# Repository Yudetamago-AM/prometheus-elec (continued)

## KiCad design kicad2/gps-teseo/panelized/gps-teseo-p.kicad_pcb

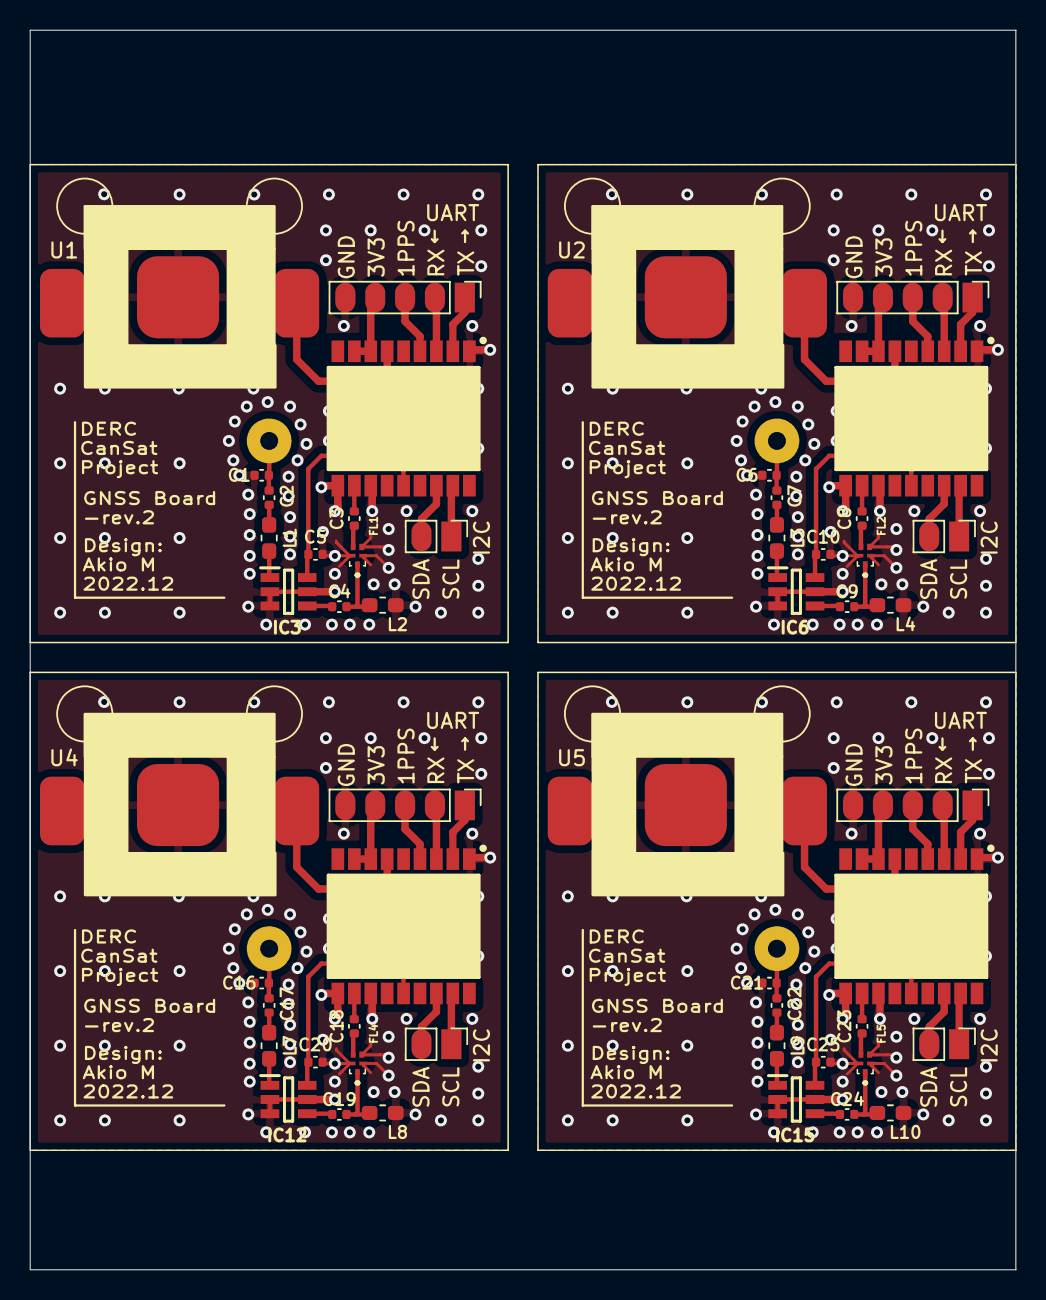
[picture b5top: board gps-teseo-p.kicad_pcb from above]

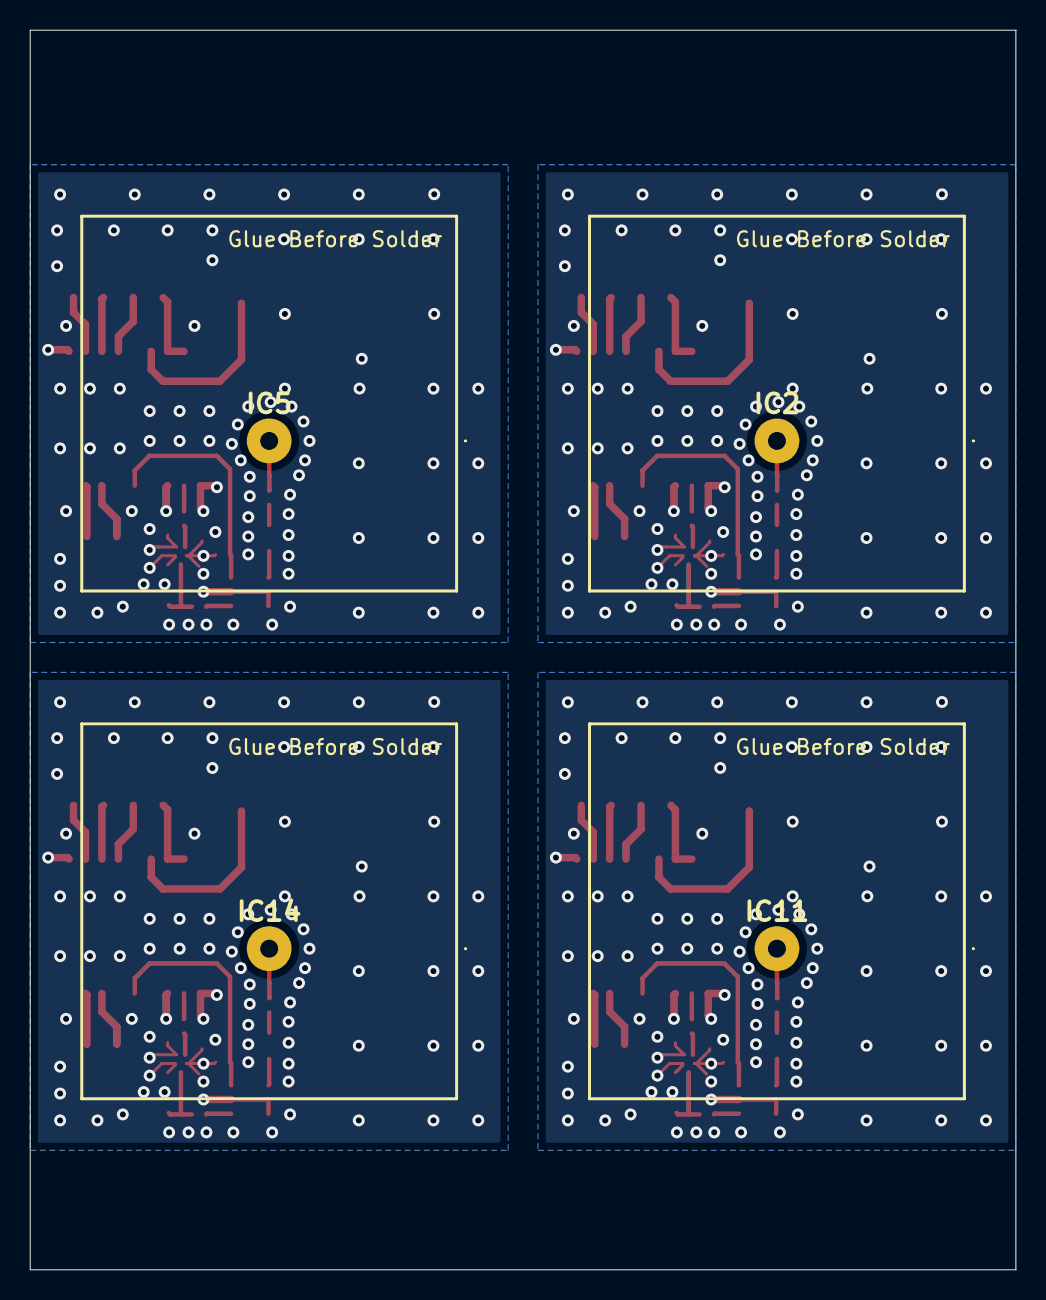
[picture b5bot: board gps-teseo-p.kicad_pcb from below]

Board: 4 copper layers, 66.0 x 83.0 mm, 56 parts (4 on the bottom side), 16 nets.

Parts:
C1, C6, C16, C21: 1p; C_0402_1005Metric
C2, C4, C7, C9, C17, C19, C22, C24: 100p; C_0402_1005Metric
C3, C8, C18, C23: 120p; C_0402_1005Metric
C5, C10, C20, C25: 470p; C_0402_1005Metric
FL1, FL2, FL4, FL5: SAFEA1G58KA0F00R15
IC1, IC4, IC10, IC13: TESEO-LIV3F; SON110P970X1010X230-18N
IC2, IC5, IC11, IC14: CGGBPD.25.A; CGGBPD25A
IC3, IC6, IC12, IC15: MAX2641EUT+T; SOT95P280X145-6N
J1, J3, J7, J9: Conn_01x05_Male; PinHeader_1x05_P2.00mm_Vertical
J2, J4, J8, J10: I2C; PinHeader_1x02_P2.00mm_Vertical
L1, L3, L7, L9: 5.6n; L_0603_1608Metric_Pad1.05x0.95mm_HandSolder
L2, L4, L8, L10: 6.8n; L_0603_1608Metric_Pad1.05x0.95mm_HandSolder
U1, U2, U4, U5: CR1025; CR1025_Holder

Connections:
+3V0: IC1.6 (VBATT), IC4.6 (VBATT), IC10.6 (VBATT), IC13.6 (VBATT), U1.2 (plus), U2.2 (plus), U4.2 (plus), U5.2 (plus)
+3V3: IC1.7 (VCC_IO), IC1.8 (VCC), IC4.7 (VCC_IO), IC4.8 (VCC), IC10.7 (VCC_IO), IC10.8 (VCC), IC13.7 (VCC_IO), IC13.8 (VCC), J1.4, J3.4, J7.4, J9.4
/GNSS_1PPS: IC1.4 (1PPS), IC4.4 (1PPS), IC10.4 (1PPS), IC13.4 (1PPS), J1.3, J3.3, J7.3, J9.3
/GNSS_RX: IC1.3 (RX), IC4.3 (RX), IC10.3 (RX), IC13.3 (RX), J1.2, J3.2, J7.2, J9.2
/GNSS_TX: IC1.2 (TX), IC4.2 (TX), IC10.2 (TX), IC13.2 (TX), J1.1, J3.1, J7.1, J9.1
/SCL: IC1.17 (SCL), IC4.17 (SCL), IC10.17 (SCL), IC13.17 (SCL), J2.1, J4.1, J8.1, J10.1
/SDA: IC1.16 (SDA), IC4.16 (SDA), IC10.16 (SDA), IC13.16 (SDA), J2.2, J4.2, J8.2, J10.2
/VCC_RF: C5.1, C10.1, C20.1, C25.1, IC1.14 (VCC_RF), IC3.6 (VCC), IC4.14 (VCC_RF), IC6.6 (VCC), IC10.14 (VCC_RF), IC12.6 (VCC), IC13.14 (VCC_RF), IC15.6 (VCC)
GND2: C1.2, C5.2, C6.2, C10.2, C16.2, C20.2, C21.2, C25.2, FL1.2 (GND_1), FL1.3 (GND_2), FL1.5 (GND_3), FL2.2 (GND_1), FL2.3 (GND_2), FL2.5 (GND_3), FL4.2 (GND_1), FL4.3 (GND_2), FL4.5 (GND_3), FL5.2 (GND_1), FL5.3 (GND_2), FL5.5 (GND_3), IC1.1 (GND), IC1.10 (GND_RF_1), IC1.12 (GND_RF_2), IC3.2 (GND_1), IC3.3 (GND_2), IC3.5 (GND_3), IC4.1 (GND), IC4.10 (GND_RF_1), IC4.12 (GND_RF_2), IC6.2 (GND_1), IC6.3 (GND_2), IC6.5 (GND_3), IC10.1 (GND), IC10.10 (GND_RF_1), IC10.12 (GND_RF_2), IC12.2 (GND_1), IC12.3 (GND_2), IC12.5 (GND_3), IC13.1 (GND), IC13.10 (GND_RF_1), IC13.12 (GND_RF_2), IC15.2 (GND_1), IC15.3 (GND_2), IC15.5 (GND_3), J1.5, J3.5, J7.5, J9.5, L2.2, L4.2, L8.2, L10.2, U1.1 (minus), U2.1 (minus), U4.1 (minus), U5.1 (minus)
unnamed: C1.1, C2.1, C6.1, C7.1, C16.1, C17.1, C21.1, C22.1, IC2.1, IC5.1, IC11.1, IC14.1
unnamed: C2.2, C7.2, C17.2, C22.2, L1.1, L3.1, L7.1, L9.1
unnamed: C3.1, C8.1, C18.1, C23.1, FL1.4 (OUT), FL2.4 (OUT), FL4.4 (OUT), FL5.4 (OUT)
unnamed: C3.2, C8.2, C18.2, C23.2, IC1.11 (RF_IN), IC4.11 (RF_IN), IC10.11 (RF_IN), IC13.11 (RF_IN)
unnamed: C4.1, C9.1, C19.1, C24.1, IC3.4 (RFOUT), IC6.4 (RFOUT), IC12.4 (RFOUT), IC15.4 (RFOUT)
unnamed: C4.2, C9.2, C19.2, C24.2, FL1.1 (IN), FL2.1 (IN), FL4.1 (IN), FL5.1 (IN), L2.1, L4.1, L8.1, L10.1
unnamed: IC3.1 (RFIN), IC6.1 (RFIN), IC12.1 (RFIN), IC15.1 (RFIN), L1.2, L3.2, L7.2, L9.2

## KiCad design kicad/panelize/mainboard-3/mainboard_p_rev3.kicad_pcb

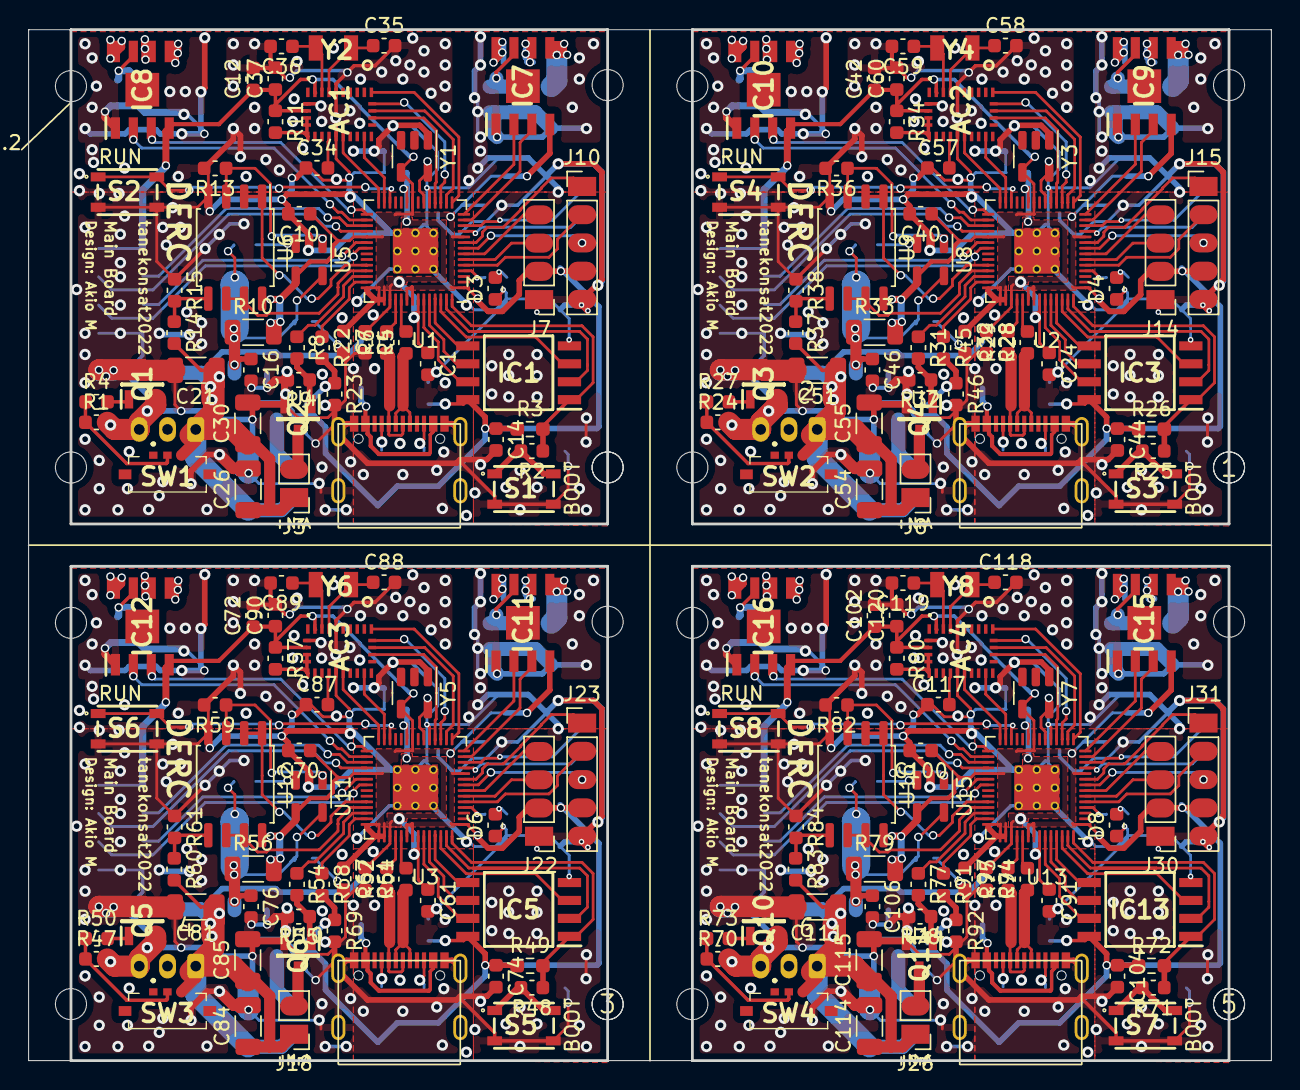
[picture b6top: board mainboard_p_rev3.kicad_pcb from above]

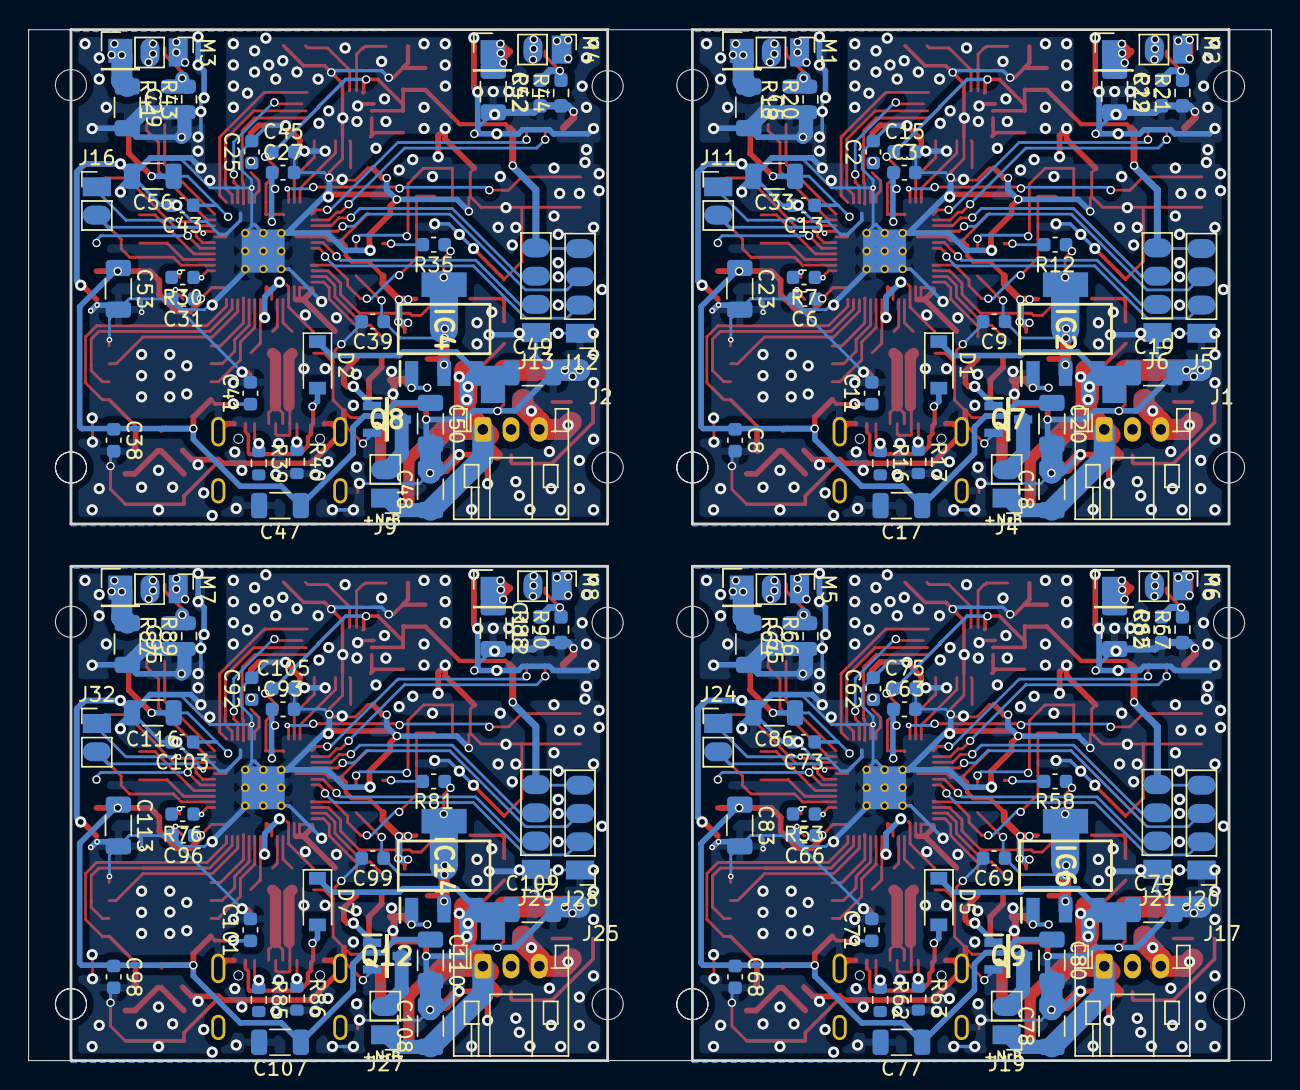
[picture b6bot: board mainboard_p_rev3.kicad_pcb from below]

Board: 2 copper layers, 88.0 x 73.0 mm, 334 parts (136 on the bottom side), 73 nets.

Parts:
1, 2, 3, 4, 5, 6: (no value)
AC1, AC2, AC3, AC4: BNO085
C1, C3, C6, C8, C10, C11, C12, C13, C14, C15, C24, C27, C31, C34, C37, C38, C40, C41, C42, C43, C44, C45, C57, C60, C61, C63, C66, C68, C70, C71, C72, C73, C74, C75, C87, C90, C91, C93, C96, C98, C100, C101, C102, C103, C104, C105, C117, C120: 100n; C_0603_1608Metric
C2, C25, C62, C92: 10p; C_0603_1608Metric
C4, C7, C9, C16, C28, C32, C39, C46, C64, C67, C69, C76, C94, C97, C99, C106: 1u; C_0603_1608Metric
C5, C17, C18, C19, C20, C21, C22, C23, C26, C29, C30, C33, C47, C48, C49, C50, C51, C52, C53, C54, C55, C56, C65, C77, C78, C79, C80, C81, C82, C83, C84, C85, C86, C95, C107, C108, C109, C110, C111, C112, C113, C114, C115, C116: 100u; C_1206_3216Metric
C35, C36, C58, C59, C88, C89, C118, C119: 22p; C_0603_1608Metric
D1, D2, D5, D7: 1N4148W; D_SOD-123
D3, D4, D6, D8: LED; C_0603_1608Metric
IC1, IC3, IC5, IC13: W25Q128JVSIQ; SOIC127P790X216-8N
IC2, IC4, IC6, IC14: ADP3338AKCZ-3.3-RL; SOT230P700X180-4N
IC7, IC8, IC9, IC10, IC11, IC12, IC15, IC16: TB67H450FNG,EL; SOIC127P600X175-9N
J1, J2, J17, J25: Conn_01x02_Male; JST_PH_S3B-PH-K_1x03_P2.00mm_Horizontal
J3, J4, J8, J9, J18, J19, J26, J27: Conn_01x02_Male; PinHeader_1x02_P2.00mm_Vertical
J5, J6, J12, J13, J20, J21, J28, J29: Conn_01x04_Male; PinHeader_1x04_P2.00mm_Vertical
J7, J14, J22, J30: Conn_01x04_Female; PinHeader_1x04_P2.00mm_Vertical
J10, J15, J23, J31: Conn_01x05_Female; PinHeader_1x05_P2.00mm_Vertical
J11, J16, J24, J32: Conn_01x02_Female; PinHeader_1x02_P2.00mm_Vertical
M1, M2, M3, M4, M5, M6, M7, M8: Motor_DC; PinHeader_1x02_P2.00mm_Vertical
Q1, Q2, Q3, Q4, Q5, Q6, Q7, Q8, Q9, Q10, Q11, Q12: Q_NMOS_DGS; SOT95P237X112-3N
R1, R4, R9, R11, R23, R24, R27, R32, R34, R46, R47, R50, R55, R57, R69, R70, R73, R78, R80, R92: 10k; C_0603_1608Metric
R2, R7, R8, R13, R15, R22, R25, R30, R31, R36, R38, R45, R48, R53, R54, R59, R61, R68, R71, R76, R77, R82, R84, R91: 1k; C_0603_1608Metric
R3, R26, R49, R72: DNF; R_0603_1608Metric_Pad0.98x0.95mm_HandSolder
R5, R6, R28, R29, R51, R52, R74, R75: 27; C_0603_1608Metric
R10, R33, R56, R79: 0.01; R_1206_3216Metric
R12, R35, R58, R81: 100; C_0603_1608Metric
R14, R37, R60, R83: 3k; C_0603_1608Metric
R16, R17, R39, R40, R62, R63, R85, R86: 5.1k; R_0603_1608Metric
R18, R19, R20, R21, R41, R42, R43, R44, R64, R65, R66, R67, R87, R88, R89, R90: R; R_0603_1608Metric_Pad0.98x0.95mm_HandSolder
S1, S2, S3, S4, S5, S6, S7, S8: SKRPACE010; SMT_4.2X3.2_
SW1, SW2, SW3, SW4: SW_DIP_x01; SSAJ120100
U1, U2, U3, U13: RP2040; RP2040-QFN-56
U4, U7, U10, U14: USB_type_C; USB_typeC_t
U5, U8, U11, U15: LT6106; SOT-23-5
U6, U9, U12, U16: Opamp_Dual; SSOP-8_5.25x5.24mm_P1.27mm
Y1, Y3, Y5, Y7: SIT2001BI-S2-33E-12.000000D; SOT-23-5
Y2, Y4, Y6, Y8: FC-135_32.768KHz_7pF_+_-20ppm; FC-135

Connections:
+1V1: C1.1, C3.1, C4.1, C24.1, C27.1, C28.1, C61.1, C63.1, C64.1, C91.1, C93.1, C94.1, U1.23 (DVDD), U1.45 (VREG_VOUT), U1.50 (DVDD), U2.23 (DVDD), U2.45 (VREG_VOUT), U2.50 (DVDD), U3.23 (DVDD), U3.45 (VREG_VOUT), U3.50 (DVDD), U13.23 (DVDD), U13.45 (VREG_VOUT), U13.50 (DVDD)
+3V3: AC1.3 (VDD), AC1.28 (VDDIO), AC2.3 (VDD), AC2.28 (VDDIO), AC3.3 (VDD), AC3.28 (VDDIO), AC4.3 (VDD), AC4.28 (VDDIO), C6.1, C7.1, C8.1, C10.1, C11.1, C12.1, C13.1, C14.1, C15.1, C17.1, C20.1, C23.1, C31.1, C32.1, C33.1, C37.1, C38.1, C40.1, C41.1, C42.1, C43.1, C44.1, C45.1, C47.1, C50.1, C53.1, C56.1, C60.1, C66.1, C67.1, C68.1, C70.1, C71.1, C72.1, C73.1, C74.1, C75.1, C77.1, C80.1, C83.1, C86.1, C90.1, C96.1, C97.1, C98.1, C100.1, C101.1, C102.1, C103.1, C104.1, C105.1, C107.1, C110.1, C113.1, C116.1, C120.1, IC1.8 (VCC), IC3.8 (VCC), IC5.8 (VCC), IC7.4 (VREF), IC8.4 (VREF), IC9.4 (VREF), IC10.4 (VREF), IC11.4 (VREF), IC12.4 (VREF), IC13.8 (VCC), IC15.4 (VREF), IC16.4 (VREF), J5.4, J6.4, J7.2, J10.4, J12.4, J13.4, J14.2, J15.4, J20.4, J21.4, J22.2, J23.4, J28.4, J29.4, J30.2, J31.4, R3.1, R10.2, R11.1, R26.1, R33.2, R34.1, R49.1, R56.2, R57.1, R72.1, R79.2, R80.1, U1.1 (IOVDD), U1.10 (IOVDD), U1.22 (IOVDD), U1.33 (IOVDD), U1.42 (IOVDD), U1.43 (ADC_AVDD), U1.44 (VREG_IN), U1.48 (USB_VDD), U1.49 (IOVDD), U2.1 (IOVDD), U2.10 (IOVDD), U2.22 (IOVDD), U2.33 (IOVDD), U2.42 (IOVDD), U2.43 (ADC_AVDD), U2.44 (VREG_IN), U2.48 (USB_VDD), U2.49 (IOVDD), U3.1 (IOVDD), U3.10 (IOVDD), U3.22 (IOVDD), U3.33 (IOVDD), U3.42 (IOVDD), U3.43 (ADC_AVDD), U3.44 (VREG_IN), U3.48 (USB_VDD), U3.49 (IOVDD), U5.4 (+), U6.8 (V+), U8.4 (+), U9.8 (V+), U11.4 (+), U12.8 (V+), U13.1 (IOVDD), U13.10 (IOVDD), U13.22 (IOVDD), U13.33 (IOVDD), U13.42 (IOVDD), U13.43 (ADC_AVDD), U13.44 (VREG_IN), U13.48 (USB_VDD), U13.49 (IOVDD), U15.4 (+), U16.8 (V+), Y1.4 (VDD), Y3.4 (VDD), Y5.4 (VDD), Y7.4 (VDD)
/3V3_REG_OUT: C9.1, C16.1, C39.1, C46.1, C69.1, C76.1, C99.1, C106.1, IC2.2 (OUT_1), IC2.4 (OUT_2), IC4.2 (OUT_1), IC4.4 (OUT_2), IC6.2 (OUT_1), IC6.4 (OUT_2), IC14.2 (OUT_1), IC14.4 (OUT_2), R10.1, R12.1, R33.1, R35.1, R56.1, R58.1, R79.1, R81.1, U5.5 (V+), U8.5 (V+), U11.5 (V+), U15.5 (V+)
/+7V4: 2.1, 4.1, 6.1, C5.1, C18.1, C19.1, C21.1, C22.1, C26.1, C29.1, C30.1, C48.1, C49.1, C51.1, C52.1, C54.1, C55.1, C65.1, C78.1, C79.1, C81.1, C82.1, C84.1, C85.1, C95.1, C108.1, C109.1, C111.1, C112.1, C114.1, C115.1, D1.1 (K), D2.1 (K), D5.1 (K), D7.1 (K), IC2.3 (IN), IC4.3 (IN), IC6.3 (IN), IC7.5 (VM), IC8.5 (VM), IC9.5 (VM), IC10.5 (VM), IC11.5 (VM), IC12.5 (VM), IC14.3 (IN), IC15.5 (VM), IC16.5 (VM), J1.1, J2.1, J3.1, J4.1, J8.1, J9.1, J17.1, J18.1, J19.1, J25.1, J26.1, J27.1, R14.2, R37.2, R60.2, R83.2, SW1.2, SW2.2, SW3.2, SW4.2
/GPIO0: U1.2 (GPIO0), U2.2 (GPIO0), U3.2 (GPIO0), U13.2 (GPIO0)
/GPIO1: U1.3 (GPIO1), U2.3 (GPIO1), U3.3 (GPIO1), U13.3 (GPIO1)
/GPIO2_LED: R7.1, R30.1, R53.1, R76.1, U1.4 (GPIO2), U2.4 (GPIO2), U3.4 (GPIO2), U13.4 (GPIO2)
/GPIO3_ToF_RST: J10.2, J15.2, J23.2, J31.2, U1.5 (GPIO3), U2.5 (GPIO3), U3.5 (GPIO3), U13.5 (GPIO3)
/GPIO4_GNSS_RX: J7.3, J14.3, J22.3, J30.3, U1.6 (GPIO4), U2.6 (GPIO4), U3.6 (GPIO4), U13.6 (GPIO4)
/GPIO5_GNSS_TX: J7.4, J14.4, J22.4, J30.4, U1.7 (GPIO5), U2.7 (GPIO5), U3.7 (GPIO5), U13.7 (GPIO5)
/GPIO6_ToF_SDA: J10.3, J15.3, J23.3, J31.3, U1.8 (GPIO6), U2.8 (GPIO6), U3.8 (GPIO6), U13.8 (GPIO6)
/GPIO7_ToF_SCL: J10.1, J15.1, J23.1, J31.1, U1.9 (GPIO7), U2.9 (GPIO7), U3.9 (GPIO7), U13.9 (GPIO7)
/GPIO8_I2C_EXT_SDA: J11.2, J16.2, J24.2, J32.2, U1.11 (GPIO8), U2.11 (GPIO8), U3.11 (GPIO8), U13.11 (GPIO8)
/GPIO9_I2C_EXT_SCL: J11.1, J16.1, J24.1, J32.1, U1.12 (GPIO9), U2.12 (GPIO9), U3.12 (GPIO9), U13.12 (GPIO9)
/GPIO10_MO_A_1: IC7.3 (IN1), IC9.3 (IN1), IC11.3 (IN1), IC15.3 (IN1), U1.13 (GPIO10), U2.13 (GPIO10), U3.13 (GPIO10), U13.13 (GPIO10)
/GPIO11_MO_A_2: IC7.2 (IN2), IC9.2 (IN2), IC11.2 (IN2), IC15.2 (IN2), U1.14 (GPIO11), U2.14 (GPIO11), U3.14 (GPIO11), U13.14 (GPIO11)
/GPIO12_IMU_MISO: AC1.20 (H_SDA/H_MISO/TX), AC2.20 (H_SDA/H_MISO/TX), AC3.20 (H_SDA/H_MISO/TX), AC4.20 (H_SDA/H_MISO/TX), U1.15 (GPIO12), U2.15 (GPIO12), U3.15 (GPIO12), U13.15 (GPIO12)
/GPIO13_IMU_CS: AC1.18 (H_CSN), AC2.18 (H_CSN), AC3.18 (H_CSN), AC4.18 (H_CSN), U1.16 (GPIO13), U2.16 (GPIO13), U3.16 (GPIO13), U13.16 (GPIO13)
/GPIO14_IMU_SCK: AC1.19 (H_SCL/SCK/RX), AC2.19 (H_SCL/SCK/RX), AC3.19 (H_SCL/SCK/RX), AC4.19 (H_SCL/SCK/RX), U1.17 (GPIO14), U2.17 (GPIO14), U3.17 (GPIO14), U13.17 (GPIO14)
/GPIO15_IMU_MOSI: AC1.17 (SA0/H_MOSI), AC2.17 (SA0/H_MOSI), AC3.17 (SA0/H_MOSI), AC4.17 (SA0/H_MOSI), U1.18 (GPIO15), U2.18 (GPIO15), U3.18 (GPIO15), U13.18 (GPIO15)
/GPIO16_IMU_INT: AC1.14 (H_INTN), AC2.14 (H_INTN), AC3.14 (H_INTN), AC4.14 (H_INTN), U1.27 (GPIO16), U2.27 (GPIO16), U3.27 (GPIO16), U13.27 (GPIO16)
/GPIO17_IMU_RST: AC1.11 (NRST), AC2.11 (NRST), AC3.11 (NRST), AC4.11 (NRST), U1.28 (GPIO17), U2.28 (GPIO17), U3.28 (GPIO17), U13.28 (GPIO17)
/GPIO18_MO_B_1: IC8.3 (IN1), IC10.3 (IN1), IC12.3 (IN1), IC16.3 (IN1), U1.29 (GPIO18), U2.29 (GPIO18), U3.29 (GPIO18), U13.29 (GPIO18)
/GPIO19_MO_B_2: IC8.2 (IN2), IC10.2 (IN2), IC12.2 (IN2), IC16.2 (IN2), U1.30 (GPIO19), U2.30 (GPIO19), U3.30 (GPIO19), U13.30 (GPIO19)
/GPIO20_MOE_A_1: J6.3, J13.3, J21.3, J29.3, U1.31 (GPIO20), U2.31 (GPIO20), U3.31 (GPIO20), U13.31 (GPIO20)
/GPIO21_MOE_B_1: J5.3, J12.3, J20.3, J28.3, U1.32 (GPIO21), U2.32 (GPIO21), U3.32 (GPIO21), U13.32 (GPIO21)
/GPIO22_MOE_A_2: J6.2, J13.2, J21.2, J29.2, U1.34 (GPIO22), U2.34 (GPIO22), U3.34 (GPIO22), U13.34 (GPIO22)
/GPIO23_MOE_B_2: J5.2, J12.2, J20.2, J28.2, U1.35 (GPIO23), U2.35 (GPIO23), U3.35 (GPIO23), U13.35 (GPIO23)
/GPIO26_ADC_I_monitor: U1.38 (GPIO26_ADC0), U2.38 (GPIO26_ADC0), U3.38 (GPIO26_ADC0), U6.1, U6.2 (-), U9.1, U9.2 (-), U12.1, U12.2 (-), U13.38 (GPIO26_ADC0), U16.1, U16.2 (-)
/GPIO27_ADC_V_monitor: U1.39 (GPIO27_ADC1), U2.39 (GPIO27_ADC1), U3.39 (GPIO27_ADC1), U6.6 (-), U6.7, U9.6 (-), U9.7, U12.6 (-), U12.7, U13.39 (GPIO27_ADC1), U16.6 (-), U16.7
/GPIO28_NichromeA: R8.1, R31.1, R54.1, R77.1, U1.40 (GPIO28_ADC2), U2.40 (GPIO28_ADC2), U3.40 (GPIO28_ADC2), U13.40 (GPIO28_ADC2)
/GPIO29_NichromeB: R22.1, R45.1, R68.1, R91.1, U1.41 (GPIO29_ADC3), U2.41 (GPIO29_ADC3), U3.41 (GPIO29_ADC3), U13.41 (GPIO29_ADC3)
/M1_MINUS: IC7.6 (OUT1), IC9.6 (OUT1), IC11.6 (OUT1), IC15.6 (OUT1), M1.2 (-), M3.2 (-), M5.2 (-), M7.2 (-)
/M1_PLUS: IC7.8 (OUT2), IC9.8 (OUT2), IC11.8 (OUT2), IC15.8 (OUT2), M1.1 (+), M3.1 (+), M5.1 (+), M7.1 (+)
/M2_MINUS: IC8.6 (OUT1), IC10.6 (OUT1), IC12.6 (OUT1), IC16.6 (OUT1), M2.2 (-), M4.2 (-), M6.2 (-), M8.2 (-)
/M2_PLUS: IC8.8 (OUT2), IC10.8 (OUT2), IC12.8 (OUT2), IC16.8 (OUT2), M2.1 (+), M4.1 (+), M6.1 (+), M8.1 (+)
/QSPI_SCLK: IC1.6 (CLK), IC3.6 (CLK), IC5.6 (CLK), IC13.6 (CLK), U1.52 (QSPI_SCLK), U2.52 (QSPI_SCLK), U3.52 (QSPI_SCLK), U13.52 (QSPI_SCLK)
/QSPI_SD0: IC1.5 (DI_(IO0)), IC3.5 (DI_(IO0)), IC5.5 (DI_(IO0)), IC13.5 (DI_(IO0)), U1.53 (QSPI_SD0), U2.53 (QSPI_SD0), U3.53 (QSPI_SD0), U13.53 (QSPI_SD0)
/QSPI_SD1: IC1.2 (DO_(IO1)), IC3.2 (DO_(IO1)), IC5.2 (DO_(IO1)), IC13.2 (DO_(IO1)), U1.55 (QSPI_SD1), U2.55 (QSPI_SD1), U3.55 (QSPI_SD1), U13.55 (QSPI_SD1)
/QSPI_SD2: IC1.3 (/WP_(IO2)), IC3.3 (/WP_(IO2)), IC5.3 (/WP_(IO2)), IC13.3 (/WP_(IO2)), U1.54 (QSPI_SD2), U2.54 (QSPI_SD2), U3.54 (QSPI_SD2), U13.54 (QSPI_SD2)
/QSPI_SD3: IC1.7 (/HOLD_OR_/RESET_(IO3)), IC3.7 (/HOLD_OR_/RESET_(IO3)), IC5.7 (/HOLD_OR_/RESET_(IO3)), IC13.7 (/HOLD_OR_/RESET_(IO3)), U1.51 (QSPI_SD3), U2.51 (QSPI_SD3), U3.51 (QSPI_SD3), U13.51 (QSPI_SD3)
/QSPI_SS: IC1.1 (/CS), IC3.1 (/CS), IC5.1 (/CS), IC13.1 (/CS), R2.1, R3.2, R25.1, R26.2, R48.1, R49.2, R71.1, R72.2, U1.56 (QSPI_SS), U2.56 (QSPI_SS), U3.56 (QSPI_SS), U13.56 (QSPI_SS)
/RUN: S2.1, S2.2, S4.1, S4.2, S6.1, S6.2, S8.1, S8.2, U1.26 (RUN), U2.26 (RUN), U3.26 (RUN), U13.26 (RUN)
/SWCLK: U1.24 (SWCLK), U2.24 (SWCLK), U3.24 (SWCLK), U13.24 (SWCLK)
/SWD: U1.25 (SWD), U2.25 (SWD), U3.25 (SWD), U13.25 (SWD)
/USB_D+: R5.1, R28.1, R51.1, R74.1, U4.6 (A6_DP1), U4.8 (B6_DP2), U7.6 (A6_DP1), U7.8 (B6_DP2), U10.6 (A6_DP1), U10.8 (B6_DP2), U14.6 (A6_DP1), U14.8 (B6_DP2)
/USB_D-: R6.1, R29.1, R52.1, R75.1, U4.5 (B7_DN2), U4.7 (A7_DN1), U7.5 (B7_DN2), U7.7 (A7_DN1), U10.5 (B7_DN2), U10.7 (A7_DN1), U14.5 (B7_DN2), U14.7 (A7_DN1)
/VBUS: D1.2 (A), D2.2 (A), D5.2 (A), D7.2 (A), U4.2 (A4-B9_VBUS), U4.11 (A9-B4_VBUS), U7.2 (A4-B9_VBUS), U7.11 (A9-B4_VBUS), U10.2 (A4-B9_VBUS), U10.11 (A9-B4_VBUS), U14.2 (A4-B9_VBUS), U14.11 (A9-B4_VBUS)
/XIN: C2.1, C25.1, C62.1, C92.1, U1.20 (XIN), U2.20 (XIN), U3.20 (XIN), U13.20 (XIN), Y1.5 (OUT), Y3.5 (OUT), Y5.5 (OUT), Y7.5 (OUT)
/XOUT: U1.21 (XOUT), U2.21 (XOUT), U3.21 (XOUT), U13.21 (XOUT)
/~USB_BOOT: R2.2, R25.2, R48.2, R71.2, S1.1, S1.2, S3.1, S3.2, S5.1, S5.2, S7.1, S7.2
GND: AC1.2 (GND_1), AC1.10 (CLKSEL0), AC1.25 (GND_2), AC2.2 (GND_1), AC2.10 (CLKSEL0), AC2.25 (GND_2), AC3.2 (GND_1), AC3.10 (CLKSEL0), AC3.25 (GND_2), AC4.2 (GND_1), AC4.10 (CLKSEL0), AC4.25 (GND_2), C1.2, C2.2, C3.2, C4.2, C5.2, C6.2, C7.2, C8.2, C9.2, C10.2, C11.2, C12.2, C13.2, C14.2, C15.2, C16.2, C17.2, C18.2, C19.2, C20.2, C21.2, C22.2, C23.2, C24.2, C25.2, C26.2, C27.2, C28.2, C29.2, C30.2, C31.2, C32.2, C33.2, C34.1, C35.2, C36.2, C37.2, C38.2, C39.2, C40.2, C41.2, C42.2, C43.2, C44.2, C45.2, C46.2, C47.2, C48.2, C49.2, C50.2, C51.2, C52.2, C53.2, C54.2, C55.2, C56.2, C57.1, C58.2, C59.2, C60.2, C61.2, C62.2, C63.2, C64.2, C65.2, C66.2, C67.2, C68.2, C69.2, C70.2, C71.2, C72.2, C73.2, C74.2, C75.2, C76.2, C77.2, C78.2, C79.2, C80.2, C81.2, C82.2, C83.2, C84.2, C85.2, C86.2, C87.1, C88.2, C89.2, C90.2, C91.2, C92.2, C93.2, C94.2, C95.2, C96.2, C97.2, C98.2, C99.2, C100.2, C101.2, C102.2, C103.2, C104.2, C105.2, C106.2, C107.2, C108.2, C109.2, C110.2, C111.2, C112.2, C113.2, C114.2, C115.2, C116.2, C117.1, C118.2, C119.2, C120.2, D3.1 (K), D4.1 (K), D6.1 (K), D8.1 (K), IC1.4 (GND), IC2.1 (GND), IC3.4 (GND), IC4.1 (GND), IC5.4 (GND), IC6.1 (GND), IC7.1 (GND), IC8.1 (GND), IC9.1 (GND), IC10.1 (GND), IC11.1 (GND), IC12.1 (GND), IC13.4 (GND), IC14.1 (GND), IC15.1 (GND), IC16.1 (GND), J5.1, J6.1, J7.1, J10.5, J12.1, J13.1, J14.1, J15.5, J20.1, J21.1, J22.1, J23.5, J28.1, J29.1, J30.1, J31.5, Q1.3 (D), Q2.2 (S), Q3.3 (D), Q4.2 (S), Q5.3 (D), Q6.2 (S), Q7.2 (S), Q8.2 (S), Q9.2 (S), Q10.3 (D), Q11.2 (S), Q12.2 (S), R9.2, R13.2, R15.1, R16.2, R17.2, R18.1, R19.1, R20.1, R21.1, R23.2, R32.2, R36.2, R38.1, R39.2, R40.2, R41.1, R42.1, R43.1, R44.1, R46.2, R55.2, R59.2, R61.1, R62.2, R63.2, R64.1, R65.1, R66.1, R67.1, R69.2, R78.2, R82.2, R84.1, R85.2, R86.2, R87.1, R88.1, R89.1, R90.1, R92.2, S1.3, S1.4, S2.3, S2.4, S3.3, S3.4, S4.3, S4.4, S5.3, S5.4, S6.3, S6.4, S7.3, S7.4, S8.3, S8.4, U1.19 (TESTEN), U1.57 (GND), U2.19 (TESTEN), U2.57 (GND), U3.19 (TESTEN), U3.57 (GND), U4.1 (A1-B12_GND), U4.12 (A12-B1_GND), U4.SHIELD, U5.2 (V-), U6.4 (V-), U7.1 (A1-B12_GND), U7.12 (A12-B1_GND), U7.SHIELD, U8.2 (V-), U9.4 (V-), U10.1 (A1-B12_GND), U10.12 (A12-B1_GND), U10.SHIELD, U11.2 (V-), U12.4 (V-), U13.19 (TESTEN), U13.57 (GND), U14.1 (A1-B12_GND), U14.12 (A12-B1_GND), U14.SHIELD, U15.2 (V-), U16.4 (V-), Y1.1 (GND), Y3.1 (GND), Y5.1 (GND), Y7.1 (GND)
GND1: J1.3 (Pin_2), J2.3 (Pin_2), J17.3 (Pin_2), J25.3 (Pin_2), Q1.2 (S), Q3.2 (S), Q5.2 (S), Q10.2 (S), R1.2, R24.2, R47.2, R70.2
unnamed: AC1.4 (BOOTN), AC1.5 (PS1), AC1.6 (PS0/WAKE), AC2.4 (BOOTN), AC2.5 (PS1), AC2.6 (PS0/WAKE), AC3.4 (BOOTN), AC3.5 (PS1), AC3.6 (PS0/WAKE), AC4.4 (BOOTN), AC4.5 (PS1), AC4.6 (PS0/WAKE), R11.2, R34.2, R57.2, R80.2
unnamed: AC1.9 (CAP), AC2.9 (CAP), AC3.9 (CAP), AC4.9 (CAP), C34.2, C57.2, C87.2, C117.2
unnamed: AC1.26 (XOUT32/CLKSEL1), AC2.26 (XOUT32/CLKSEL1), AC3.26 (XOUT32/CLKSEL1), AC4.26 (XOUT32/CLKSEL1), C35.1, C58.1, C88.1, C118.1, Y2.1, Y4.1, Y6.1, Y8.1
unnamed: AC1.27 (XIN32), AC2.27 (XIN32), AC3.27 (XIN32), AC4.27 (XIN32), C36.1, C59.1, C89.1, C119.1, Y2.2, Y4.2, Y6.2, Y8.2
unnamed: D3.2 (A), D4.2 (A), D6.2 (A), D8.2 (A), R7.2, R30.2, R53.2, R76.2
unnamed: IC7.7 (RS), IC9.7 (RS), IC11.7 (RS), IC15.7 (RS), R18.2, R20.2, R41.2, R43.2, R64.2, R66.2, R87.2, R89.2
unnamed: IC8.7 (RS), IC10.7 (RS), IC12.7 (RS), IC16.7 (RS), R19.2, R21.2, R42.2, R44.2, R65.2, R67.2, R88.2, R90.2
unnamed: J3.2, J8.2, J18.2, J26.2, Q2.3 (D), Q4.3 (D), Q6.3 (D), Q11.3 (D)
unnamed: J4.2, J9.2, J19.2, J27.2, Q7.3 (D), Q8.3 (D), Q9.3 (D), Q12.3 (D)
unnamed: Q1.1 (G), Q3.1 (G), Q5.1 (G), Q10.1 (G), R4.2, R27.2, R50.2, R73.2
unnamed: Q2.1 (G), Q4.1 (G), Q6.1 (G), Q11.1 (G), R8.2, R9.1, R31.2, R32.1, R54.2, R55.1, R77.2, R78.1
unnamed: Q7.1 (G), Q8.1 (G), Q9.1 (G), Q12.1 (G), R22.2, R23.1, R45.2, R46.1, R68.2, R69.1, R91.2, R92.1
unnamed: R1.1, R4.1, R24.1, R27.1, R47.1, R50.1, R70.1, R73.1, SW1.C1, SW2.C1, SW3.C1, SW4.C1
unnamed: R5.2, R28.2, R51.2, R74.2, U1.47 (USB_DP), U2.47 (USB_DP), U3.47 (USB_DP), U13.47 (USB_DP)
unnamed: R6.2, R29.2, R52.2, R75.2, U1.46 (USB_DM), U2.46 (USB_DM), U3.46 (USB_DM), U13.46 (USB_DM)
unnamed: R12.2, R35.2, R58.2, R81.2, U5.3 (-), U8.3 (-), U11.3 (-), U15.3 (-)
unnamed: R13.1, R36.1, R59.1, R82.1, U5.1, U6.3 (+), U8.1, U9.3 (+), U11.1, U12.3 (+), U15.1, U16.3 (+)
unnamed: R14.1, R15.2, R37.1, R38.2, R60.1, R61.2, R83.1, R84.2, U6.5 (+), U9.5 (+), U12.5 (+), U16.5 (+)
unnamed: R16.1, R39.1, R62.1, R85.1, U4.10 (B5_CC2), U7.10 (B5_CC2), U10.10 (B5_CC2), U14.10 (B5_CC2)
unnamed: R17.1, R40.1, R63.1, R86.1, U4.4 (A5_CC1), U7.4 (A5_CC1), U10.4 (A5_CC1), U14.4 (A5_CC1)

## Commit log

2022-08-06 update schematic
2022-08-20 update IMU level shift
2022-08-27 update power section & interface
2022-08-31 schematic circuit diagram (almost) done!
2022-08-31 done! AW of GNSS board
2022-09-19 update 9-axis sensor
2022-09-19 add kicad library
2022-09-19 done AW of main board
2022-09-19 panelized main board
2022-09-29 add sketch
2022-10-09 added newest version:)
2022-10-14 release ver1
2022-10-15 GPS thickness and wiring changed
2022-10-15 new front and back body
2022-10-17 temporal uplpad change made a bit
2022-10-17 battery haisenn added
2022-10-17 incase
2022-10-19 incase of emergency
2022-10-20 20th ver
2022-10-21 temporary
2022-10-22 update conn
2022-10-22 add altium ver
2022-10-24 base assembly added
2022-10-25 update schematic in altium
2022-10-26 update footprint
2022-10-27 instance2
2022-10-27 base complete yeasssssssssss
2022-11-03 update footprints
2022-11-03 add altium library
2022-11-03 add pcb rules and some wire
2022-11-04 add new tail tail11-4
2022-11-06 add body moter middle ver
2022-11-07 add tire
2022-11-08 add lemon body shape assembly
2022-11-11 add assembly without tire
2022-11-14 add base lemon shape assembly new
2022-11-14 add assembly not working
2022-11-18 asse complete
2022-11-22 add new kicad proj
2022-11-23 update pcb
2022-11-23 salvage kicad_sym
2022-11-23 complete prometheus-em pcb
2022-11-30 add body back and tire print complete version
2022-12-01 add body asse for print
2022-12-04 add body renewed after first proper print. holes are closed and side side changed to 50mm
2022-12-04 add front and back after first proper 3D print. side 50mm
2022-12-05 update kicad pcb
2022-12-05 add gnss-board rev2 and main-board rev3
2022-12-08 add body back for ptint 12.8
2022-12-08 update body
2022-12-15 add body front and back back for print 12.5 GNSS and first alminium 1.2mm
2022-12-18 update sch & pcb (em-rev4!)
2022-12-19 add bayonet mount
2022-12-19 changed level-shifter
2022-12-19 404 sunday data not found shit
2022-12-21 add whole body for printing. tail in progress
2022-12-22 update bayonet mount
2022-12-22 tale
2022-12-23 newfolders
2022-12-23 tailbaseadd
2022-12-28 last commit of sch/pcb, prepare to move
2022-12-28 remove machinary files
2022-12-29 update main board pcb, add ublox-m10s pcb
2023-01-05 add eeprom for log
2023-01-30 add ir feature
